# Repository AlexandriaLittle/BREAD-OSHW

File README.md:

# BREAD - Broadly Reconfigurable and Expandable Automation Device

## How to use
**Please check the Documentation folder for the original research paper and how-to guides!**

## Original Authors
The original project documentation is published in the open-access journal Hardware X 15 and is authored by Shane Oberloier, Nicholas G. Whisman, Finn Hafting, and Joshua M. Pearce. Other contributors have added to the body of work since. Please refer to the original sources (below) for important details about licensing, contributors, and any updates.

## About this repository
This is not an 'official' or even necessarily a current collection of all of these collected projects. Please see the links below to download from their original sources. The projects are collected here mostly for convenient access and learning.

## License
As the original project is licensed CC-BY-SA-4.0, this project is released under the same license. Social share image source https://www.appropedia.org/w/index.php?curid=122111.

## BREAD Links
- [Finn Hafting: Modularize your electronics with BREAD - YouTube](https://www.youtube.com/watch?v=OMPlVbqSqJ4)
- [Open Source Framework: Expandable Reconfigurable Data Acquisition Device (BREAD)](https://www.appropedia.org/Open_Source_Framework_for_a_Broadly_Expandable_and_Reconfigurable_Data_Acquisition_and_Automation_Device_(BREAD))
- [OSHE Bread Applications - Appropedia, the sustainability wiki](https://www.appropedia.org/OSHE_Bread_Applications)
- [GitHub - FHafting/BREAD](https://github.com/FHafting/BREAD)
- [OSF | BREAD](https://osf.io/u2h4g/overview)
- [OSF | LOAF_x04 Backplane](https://osf.io/7mk4w/overview)
- [OSF | BREAD LOAF_x08](https://osf.io/x4yqj/overview)
- [OSF | BREAD Slice - +/- 10A Current Sensor (SLC_CR10)](https://osf.io/ajmbe/overview)
- [OSF | BREAD Slice - +/- 20A Current Sensor (SLC_CR20)](https://osf.io/xe6cz/overview)
- [OSF | BREAD Slice - +/- 40A Current Sensor (SLC_CR40)](https://osf.io/xpgf8/overview)
- [OSF | BREAD Slice - 4 Channel Relay (SLC_RLAY)](https://osf.io/5vxws/overview)
- [OSF | BREAD Slice - Audio Analysis (SLC_AAFT)](https://osf.io/a8nk5/overview)
- [OSF | BREAD Slice - Bioreactor (SPECIALIZED) (SLC_PHDO)](https://osf.io/zbg98/overview)
- [OSF | BREAD Slice - BLDC Motor Controller](https://osf.io/w9rka/overview)
- [OSF | BREAD Slice - DC Motor Controller (SLC_DCMT)](https://osf.io/6aw9m/overview)
- [OSF | BREAD Slice - Field Solar Power (SLC_SOLR)](https://osf.io/9gm5h/overview)
- [OSF | BREAD Slice - MOLD(Mass Output and Logging Device)](https://osf.io/nm7je/overview)
- [OSF | BREAD Slice - Pressure Sensor](https://osf.io/86dz7/overview)
- [OSF | BREAD Slice - Pump Control Board (Specialized) (SLC_PUMP)](https://osf.io/4mzs8/overview)
- [OSF | BREAD Slice - Relay Heating Element Controller (SLC_RLHT)](https://osf.io/pf6gy/overview)
- [OSF | BREAD Slice - Servo Motor Controller (SLC_SERV)](https://osf.io/d7vks/overview)
- [OSF | BREAD Slice - Stepper Motor Controller (SLC_STEP)](https://osf.io/q8nkc/overview)
- [OSF | BREAD Slice - Template (SLC_TEMP)](https://osf.io/v5327/overview)
- [OSF | BREAD Slice - Text-to-Speech](https://osf.io/erbp6/overview)
- [OSF | BREAD Slice - Thermocouple Reader (SLC_THRM)](https://osf.io/sfehu/overview)
- [OSF | BREAD Slice - USB Port (SLC_USBP)](https://osf.io/j9rh5/overview)
- [OSF | BREAD Slice -- Analog Reader / FFT (SLC_LVAI)](https://osf.io/742ez/overview)
- [OSF | BREAD Slice -- Battery Management (SLC_BMS)](https://osf.io/yrmqu/overview)
- [OSF | BREAD Slice -- Buck Converter / Analog Signal Generator (SLC_BUCK)](https://osf.io/2xpnu/overview)
- [OSF | BREAD Slice-- Heating Element Controller (SLC_HEAT)](https://osf.io/m53fu/overview)
- [OSF | BREAD BUNS](https://osf.io/hbz92/overview)
- [OSF | BREAD CAN update](https://osf.io/3rnj4/overview)
- [OSF | BREAD DAQ](https://osf.io/wxt3s/overview)
- [OSF | BREAD Vision](https://osf.io/2htbm/overview)
- [OSF | Off-Grid BREAD](https://osf.io/98m6k/overview)
- [OSF | Integrated Open Source Pyrolysis Board based on BREAD](https://osf.io/3ugbn/overview)
- [Shane Oberloier | BREAD Contributor](https://osf.io/user/fntgd)
- [Nicholas Whisman | BREAD Contributor](https://osf.io/user/zs4mx?tab=2)
- [Finn Hafting | BREAD Contributor](https://osf.io/user/78mv4?tab=2)
- [BREAD References and Citations](https://ouci.dntb.gov.ua/en/works/lxXvAPQl/)
- [Open Source Hardware Enterprise](https://oshe.io/)
- [Original Project Logo](https://www.appropedia.org/w/index.php?curid=122111)

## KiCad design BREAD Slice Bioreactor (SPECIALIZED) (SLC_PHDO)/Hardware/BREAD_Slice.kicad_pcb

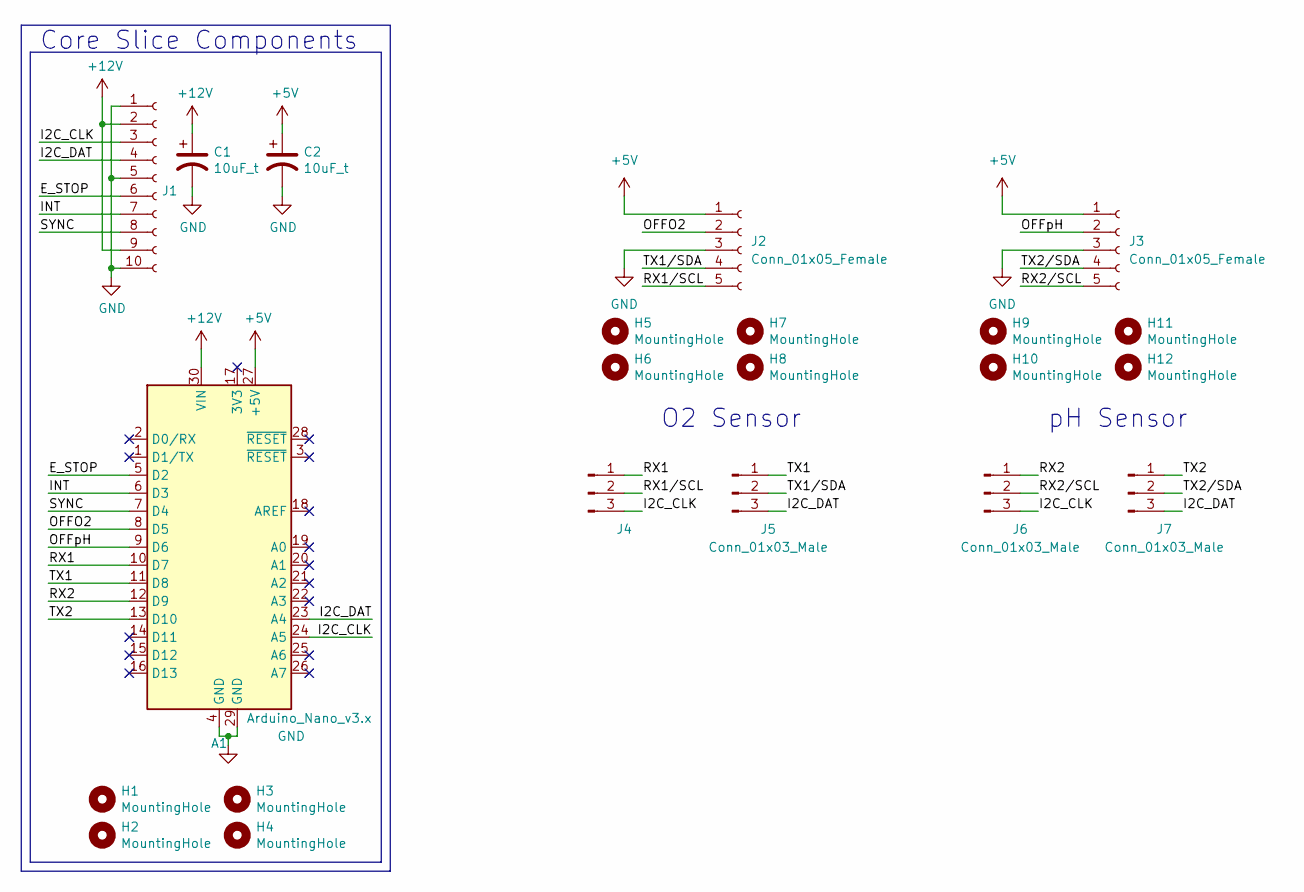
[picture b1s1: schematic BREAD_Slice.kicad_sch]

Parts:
A1: Arduino_Nano_v3.x; Arduino_Nano
C1, C2: 10uF_t; C_1206_3216Metric_Pad1.33x1.80mm_HandSolder; Part # T491C106K025AT
H1, H2, H3, H4, H5, H6, H7, H8, H9, H10, H11, H12: MountingHole; MountingHole_3.2mm_M3_DIN965_Pad
J1: Conn_01x10_Female; PinSocket_1x10_P2.54mm_Horizontal
J2, J3: Conn_01x05_Female; PinSocket_1x05_P2.54mm_Vertical
J4: (no value)
J5: Conn_01x03_Male
J6, J7: Conn_01x03_Male; PinSocket_1x03_P2.54mm_Vertical

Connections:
+5V: A1.27 (+5V), C2.1, J2.1, J3.1
+12V: A1.30 (VIN), C1.1, J1.2, J1.9
/E_STOP: A1.5 (D2), J1.6
/I2C_CLK: A1.24 (A5), J1.3, J4.3, J6.3
/I2C_DAT: A1.23 (A4), J1.4, J5.3, J7.3
/INT: A1.6 (D3), J1.7
/OFFO2: A1.8 (D5), J2.2
/OFFpH: A1.9 (D6), J3.2
/RX1: A1.10 (D7), J4.1
/RX1/SCL: J2.5, J4.2
/RX2: A1.12 (D9), J6.1
/RX2/SCL: J3.5, J6.2
/SYNC: A1.7 (D4), J1.8
/TX1: A1.11 (D8), J5.1
/TX1/SDA: J2.4, J5.2
/TX2: A1.13 (D10), J7.1
/TX2/SDA: J3.4, J7.2
GND: A1.4 (GND), A1.29 (GND), C1.2, C2.2, J1.1, J1.5, J1.10, J2.3, J3.3

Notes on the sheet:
O2 Sensor
pH Sensor
Core Slice Components

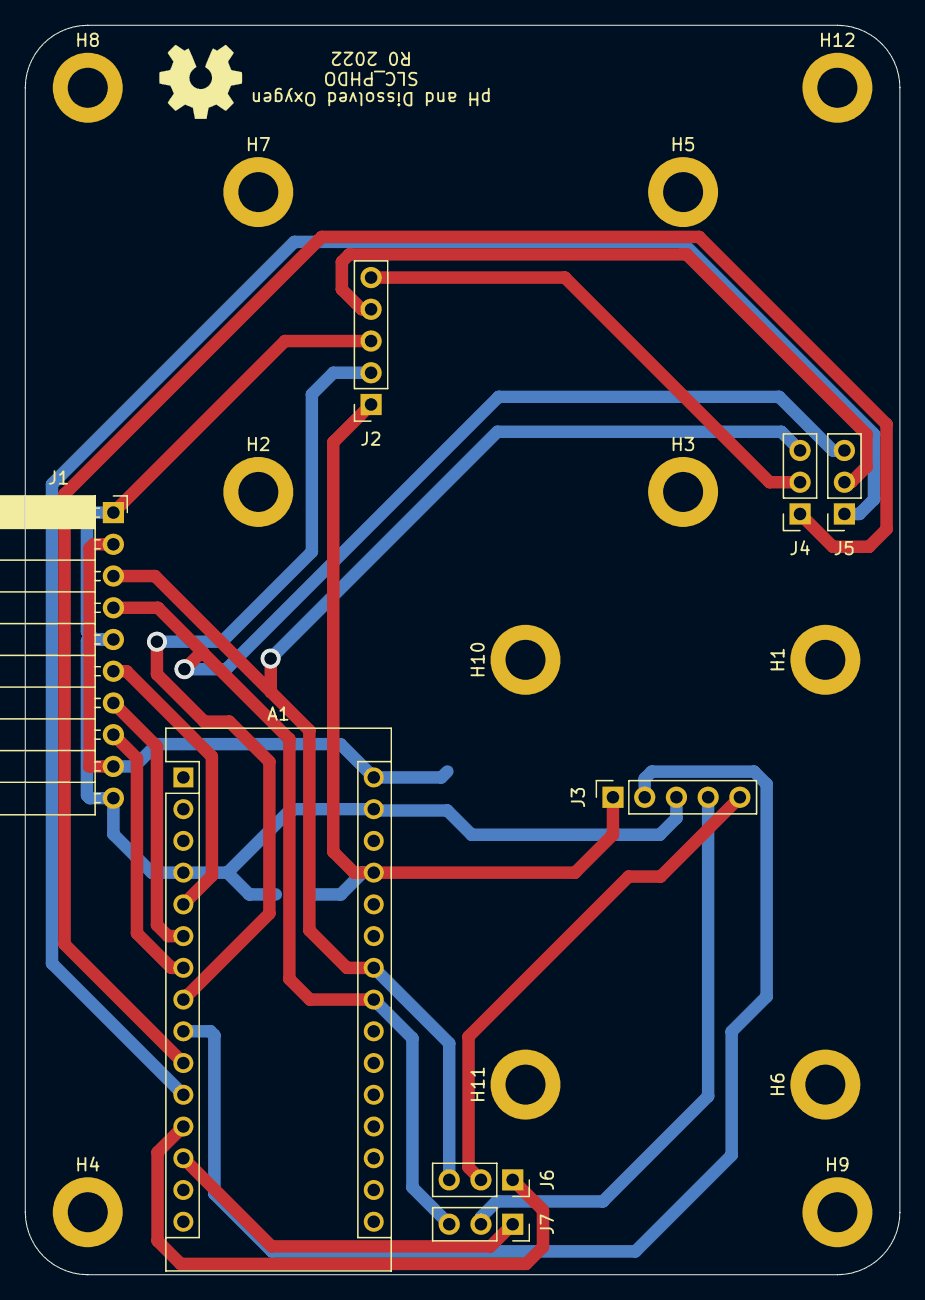
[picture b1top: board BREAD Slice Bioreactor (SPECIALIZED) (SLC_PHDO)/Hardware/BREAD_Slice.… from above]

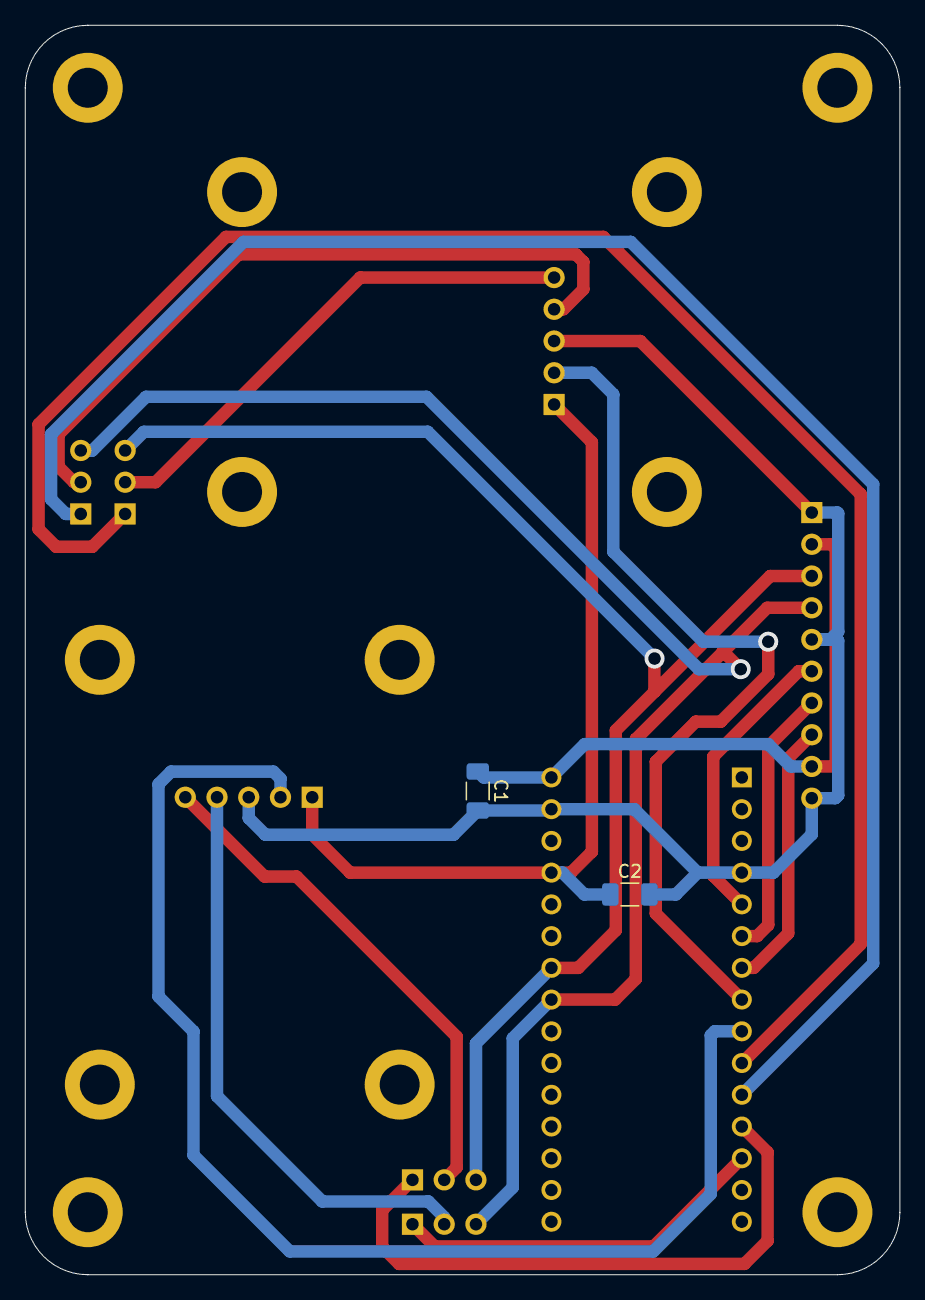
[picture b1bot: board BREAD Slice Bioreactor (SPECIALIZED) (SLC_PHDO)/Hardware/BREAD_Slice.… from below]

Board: 2 copper layers, 70.0 x 100.0 mm, 23 parts (2 on the bottom side), 18 nets.

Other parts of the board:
Logo1: Logo_Open_Hardware_Small; OSHW-Symbol_6.7x6mm_SilkScreen

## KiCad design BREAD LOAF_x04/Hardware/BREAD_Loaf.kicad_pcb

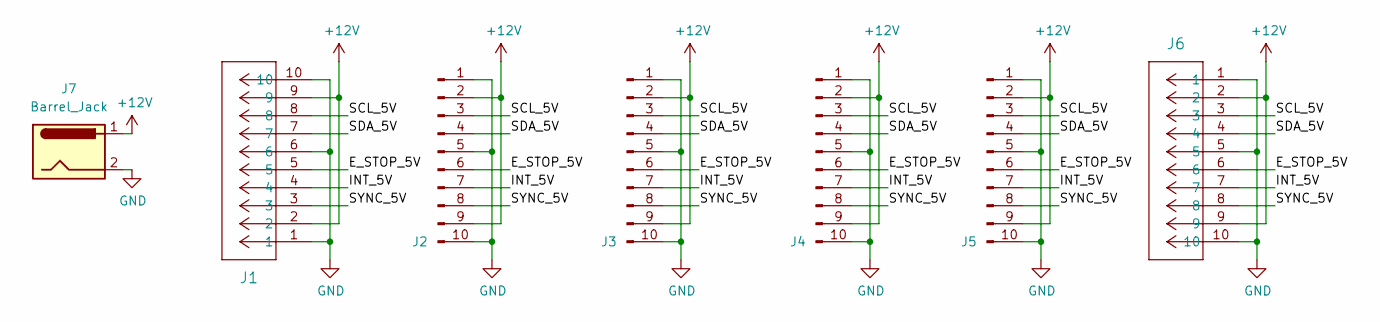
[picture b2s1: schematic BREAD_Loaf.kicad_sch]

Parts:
J1: PPPC101LGBN-RC; 1x10 RA Male Header 2.54mm Pitch
J2, J3, J4, J5: Conn_01x10_Male; BREAD 10-Pin Connector
J6: PPPC101LGBN-RC; PinSocket_1x10_P2.54mm_Horizontal
J7: Barrel_Jack; BarrelJack_CUI_PJ-063AH_Horizontal

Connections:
+12V: J1.2, J1.9, J2.2, J2.9, J3.2, J3.9, J4.2, J4.9, J5.2, J5.9, J6.2, J6.9, J7.1
/E_STOP_5V: J1.5, J2.6, J3.6, J4.6, J5.6, J6.6
/INT_5V: J1.4, J2.7, J3.7, J4.7, J5.7, J6.7
/SCL_5V: J1.8, J2.3, J3.3, J4.3, J5.3, J6.3
/SDA_5V: J1.7, J2.4, J3.4, J4.4, J5.4, J6.4
/SYNC_5V: J1.3, J2.8, J3.8, J4.8, J5.8, J6.8
GND: J1.1, J1.6, J1.10, J2.1, J2.5, J2.10, J3.1, J3.5, J3.10, J4.1, J4.5, J4.10, J5.1, J5.5, J5.10, J6.1, J6.5, J6.10, J7.2

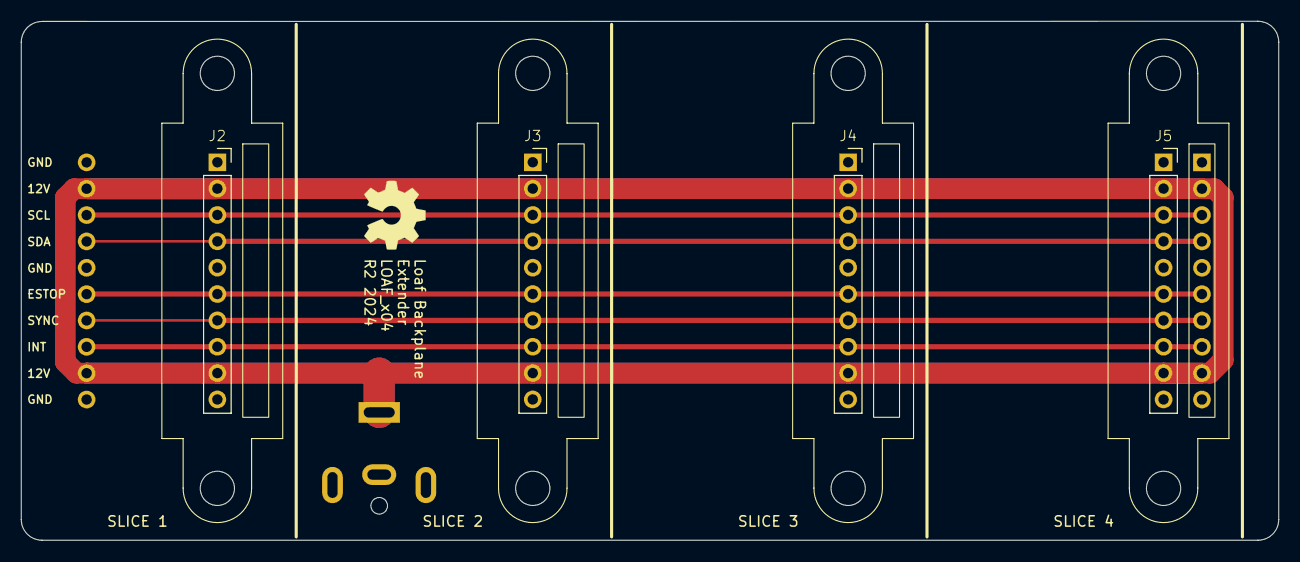
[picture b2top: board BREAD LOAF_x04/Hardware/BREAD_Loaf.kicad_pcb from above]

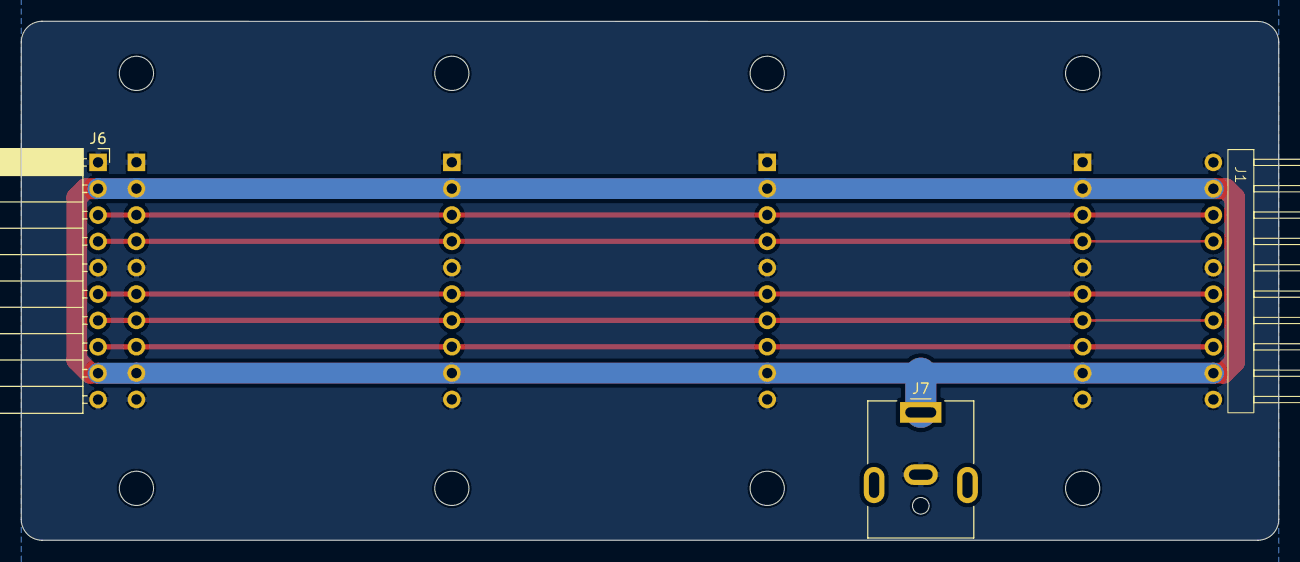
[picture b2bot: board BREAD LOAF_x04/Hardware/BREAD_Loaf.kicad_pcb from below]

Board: 2 copper layers, 121.2 x 50.0 mm, 8 parts (3 on the bottom side), 7 nets.

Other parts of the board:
Logo1: Logo_Open_Hardware_Small; OSHW-Symbol_6.7x6mm_SilkScreen

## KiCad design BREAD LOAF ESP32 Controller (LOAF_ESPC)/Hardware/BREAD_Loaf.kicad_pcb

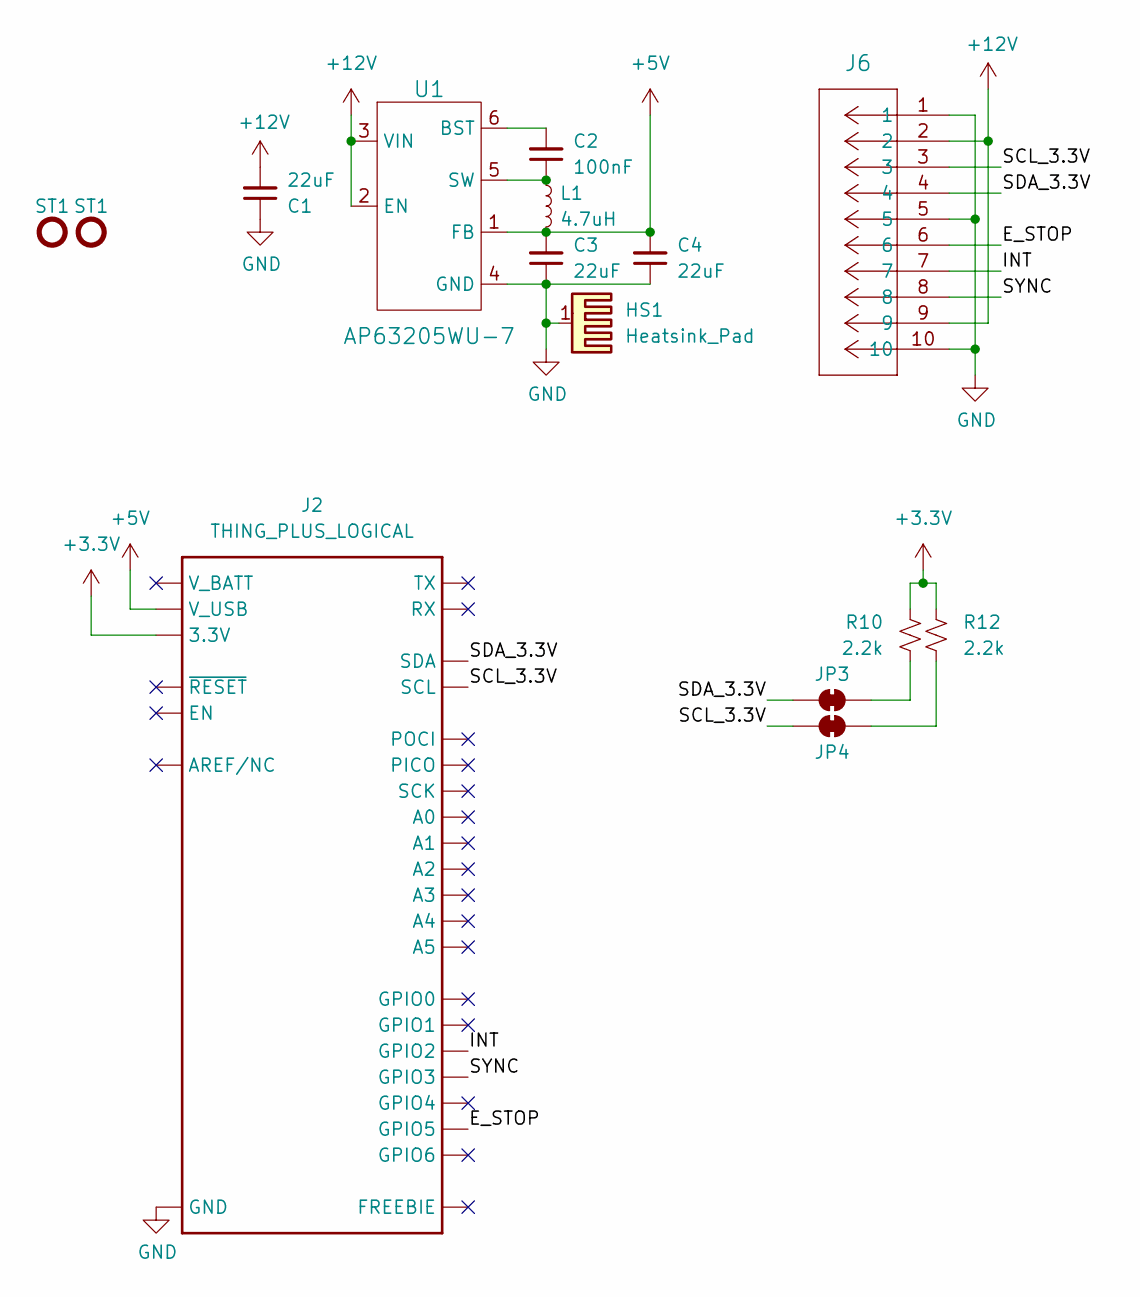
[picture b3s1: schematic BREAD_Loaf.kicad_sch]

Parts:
C1, C3, C4: 22uF; C_1206_3216Metric
C2: 100nF; C_1206_3216Metric
HS1: Heatsink_Pad; Thermal Pad
J2: THING_PLUS_LOGICAL; ESP_THING_PLUS
J6: PPPC101LGBN-RC; PinSocket_1x10_P2.54mm_Horizontal
JP3, JP4: SMT-JUMPER_2_NC_TRACE_SILK
L1: 4.7uH; L_1210_3225Metric
R10, R12: 2.2k; R_0603_1608Metric
ST1: Stand_off; STAND-OFF
U1: AP63205WU-7; TSOT-23-6

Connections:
+3.3V: J2.27 (3.3V), R10.1, R12.1
+5V: C3.2, C4.2, J2.10 (V_USB), L1.2; also elsewhere on the board
+12V: C1.2, J6.2, J6.9; also elsewhere on the board
/E_STOP: J2.4 (GPIO5), J6.6
/INT: J2.7 (GPIO2), J6.7
/SCL_3.3V: J2.2 (SCL), J6.3, JP4.2 (B)
/SDA_3.3V: J2.1 (SDA), J6.4, JP3.2 (B)
/SYNC: J2.6 (GPIO3), J6.8
GND: C1.1, C3.1, C4.1, HS1.1, J2.25 (GND), J6.1, J6.5, J6.10; also elsewhere on the board
unnamed: JP3.1 (A), R10.2
unnamed: JP4.1 (A), R12.2
unnamed 11: C2.2; also elsewhere on the board
unnamed 12: C2.1, L1.1; also elsewhere on the board

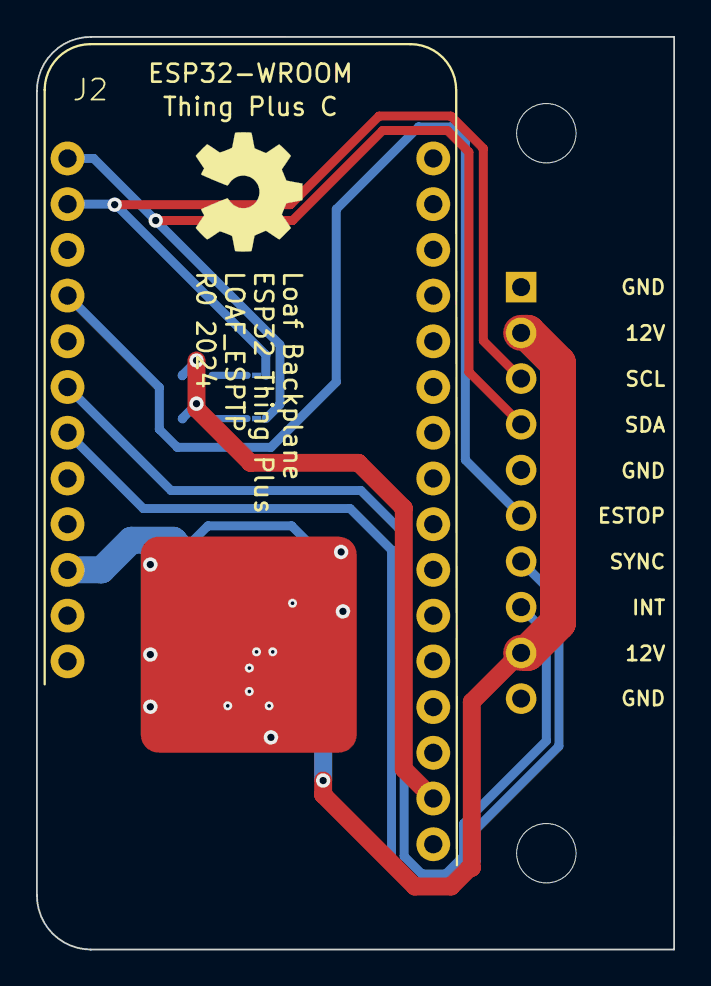
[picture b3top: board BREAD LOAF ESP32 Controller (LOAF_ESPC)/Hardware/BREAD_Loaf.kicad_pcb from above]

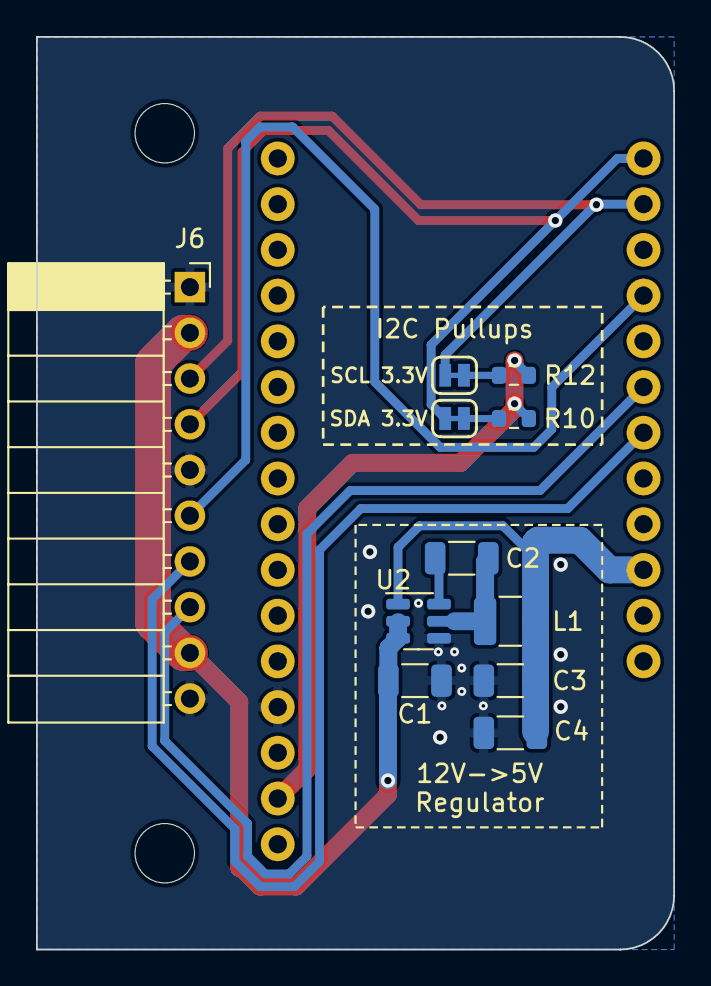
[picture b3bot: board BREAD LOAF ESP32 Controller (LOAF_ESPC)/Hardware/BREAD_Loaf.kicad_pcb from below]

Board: 2 copper layers, 35.4 x 50.7 mm, 16 parts (11 on the bottom side), 13 nets.

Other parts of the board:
Logo1: Logo_Open_Hardware_Small; OSHW-Symbol_6.7x6mm_SilkScreen
ST2: Stand_off; STAND-OFF
U2: AP63205WU-7; TSOT-23-6

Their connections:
+5V: U2.1 (FB); also elsewhere on the board
+12V: U2.2 (EN), U2.3 (VIN); also elsewhere on the board
GND: U2.4 (GND); also elsewhere on the board
unnamed 11: U2.6 (BST); also elsewhere on the board
unnamed 12: U2.5 (SW); also elsewhere on the board

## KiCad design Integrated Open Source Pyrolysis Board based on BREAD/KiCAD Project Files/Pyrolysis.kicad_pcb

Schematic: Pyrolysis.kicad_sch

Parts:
A1, A2, A3, A4, A5: Arduino_Nano_v3.x; Arduino_Nano
C1, C2, C3, C4, C8, C9, C12, C13, C14, C15, C16: 0.01 uF; C_1206_3216Metric_Pad1.33x1.80mm_HandSolder
C5, C10, C11: 10uF; C_1206_3216Metric_Pad1.33x1.80mm_HandSolder
C6, C7, C17: 10 nF; C_1206_3216Metric_Pad1.33x1.80mm_HandSolder
D1, D2, D3, D4, D5, D6, D7, D8, D9, D10: General_Purpose_Diode; D_DO-35_SOD27_P7.62mm_Horizontal; Part # 1N914BWS
F1, F2, F3, F4, F5, F6, F7, F8, F9, F10: 10A; Fuse_Holder; Part # 3522-2
FB1, FB2, FB3, FB4, FB5, FB6, FB7, FB8, FB9, FB10, FB11, FB12, FB13, FB14, FB15, FB16, FB17, FB18, FB19, FB20, FB21, FB22: Ferrite_Bead_Small; R_1206_3216Metric_Pad1.30x1.75mm_HandSolder
H1, H2, H3, H4: MountingHole; MountingHole_3.2mm_M3_DIN965_Pad
J1, J2, J3, J4, J5, J6, J7, J9, J11, J12, J15, J16, J17, J21, J22, J23, J27, J28, J29, J30, J32, J33, J34, J36, J37, J39, J40, J41, J43, J44, J45, J47, J48: Term_2; TerminalBlock_Phoenix_MKDS-1,5-2_1x02_P5.00mm_Horizontal; Part # 1935161
J8: Conn_01x03_Male; PinSocket_1x03_P2.54mm_Vertical
J10: Screw_Terminal_01x04; TerminalBlock_TE_282834-4_1x04_P2.54mm_Horizontal
J13: Conn_01x03_Male; PinHeader_1x03_P2.54mm_Vertical
J26: Barrel_Jack; BarrelJack_CUI_PJ-102AH_Horizontal
K1, K2, K3, K4, K5, K6, K7, K8, K9, K10: G5Q-1; Relay_SPDT_Omron-G5Q-1
R1: 2.2 k; R_1206_3216Metric_Pad1.30x1.75mm_HandSolder
U1, U4, U5, U8, U11, U14, U16, U18, U20, U22: TCMT1100; SOP-4_4.4x2.6mm_P1.27mm
U2, U3, U6, U7, U10, U13, U15, U17, U19, U21, U23: MAX6675ISA+; SO08-MAX6675
U12: AP1117-50; SOT-223-3_TabPin2
U24: LMD18200; TO-220-11_P3.4x5.08mm_StaggerOdd_Lead4.85mm_Vertical

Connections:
+5V: A1.27 (+5V), A2.27 (+5V), A3.27 (+5V), A4.27 (+5V), A5.27 (+5V), C11.1, J10.3, U2.4 (VCC), U3.4 (VCC), U6.4 (VCC), U7.4 (VCC), U10.4 (VCC), U12.2 (VO), U13.4 (VCC), U15.4 (VCC), U17.4 (VCC), U19.4 (VCC), U21.4 (VCC), U23.4 (VCC)
+12V: C10.1, F1.2, F2.2, F3.2, F4.2, F5.2, F6.2, F7.2, F8.2, F9.2, F10.2, J8.2, J26.1, U12.3 (VI)
/3V3: A3.17 (3V3)
/A1: A3.19 (A0), J10.1
/B1: A3.20 (A1), J10.2
/BR1: A3.9 (D6), U24.4 (BRAKE)
/CLK1: A2.16 (D13), U3.5 (SCK), U7.5 (SCK), U10.5 (SCK)
/CLK2: A4.16 (D13), U13.5 (SCK), U15.5 (SCK), U17.5 (SCK)
/CLK3: A5.16 (D13), U19.5 (SCK), U21.5 (SCK), U23.5 (SCK)
/CLK4: A1.16 (D13), U2.5 (SCK), U6.5 (SCK)
/CSEN1: A3.25 (A6), C17.1, R1.1, U24.8 (CURRENT_SENSE_OUTPUT)
/CUST1: J8.1, J11.1
/DATA1: A2.15 (D12), U3.7 (SO), U7.7 (SO), U10.7 (SO)
/DATA2: A4.15 (D12), U13.7 (SO), U15.7 (SO), U17.7 (SO)
/DATA3: A5.15 (D12), U19.7 (SO), U21.7 (SO), U23.7 (SO)
/DATA4: A1.15 (D12), U2.7 (SO), U6.7 (SO)
/DIR1: A3.10 (D7), U24.3 (DIRECTION)
/I2C_CLK: A1.24 (A5), A2.24 (A5), A3.24 (A5), A4.24 (A5), A5.24 (A5), J13.2
/I2C_DAT: A1.23 (A4), A2.23 (A4), A3.23 (A4), A4.23 (A4), A5.23 (A4), J13.1
/MC1: A3.12 (D9), U24.5 (PWM)
/PWM1: A2.8 (D5), U1.1
/PWM2: A2.9 (D6), U5.1
/PWM3: A2.10 (D7), U8.1
/PWM4: A4.8 (D5), U11.1
/PWM5: A4.9 (D6), U14.1
/PWM6: A4.10 (D7), U16.1
/PWM7: A5.8 (D5), U18.1
/PWM8: A5.9 (D6), U20.1
/PWM9: A5.10 (D7), U22.1
/PWM10: A1.10 (D7), U4.1
/SS1: A2.12 (D9), U3.6 (~CS)
/SS2: A2.13 (D10), U7.6 (~CS)
/SS3: A2.14 (D11), U10.6 (~CS)
/SS4: A4.12 (D9), U13.6 (~CS)
/SS5: A4.13 (D10), U15.6 (~CS)
/SS6: A4.14 (D11), U17.6 (~CS)
/SS7: A5.12 (D9), U19.6 (~CS)
/SS8: A5.13 (D10), U21.6 (~CS)
/SS9: A5.14 (D11), U23.6 (~CS)
/SS10: A1.13 (D10), U2.6 (~CS)
/SS11: A1.14 (D11), U6.6 (~CS)
/T+1: C1.1, FB1.1, U3.3 (T+)
/T+2: C4.1, FB5.1, U7.3 (T+)
/T+3: C8.1, FB7.1, U10.3 (T+)
/T+4: C9.1, FB9.1, U13.3 (T+)
/T+5: C12.1, FB11.1, U15.3 (T+)
/T+6: C13.1, FB13.1, U17.3 (T+)
/T+7: C14.1, FB15.1, U19.3 (T+)
/T+8: C15.1, FB17.1, U21.3 (T+)
/T+9: C16.1, FB19.1, U23.3 (T+)
/T+10: C2.1, FB3.1, U2.3 (T+)
/T+11: C3.1, FB21.1, U6.3 (T+)
/THRM1: A3.8 (D5), U24.9 (~THERMAL_FLAG_OUTPUT)
GND: A1.4 (GND), A1.29 (GND), A2.4 (GND), A2.29 (GND), A3.4 (GND), A3.29 (GND), A4.4 (GND), A4.29 (GND), A5.4 (GND), A5.29 (GND), C1.2, C2.2, C3.2, C4.2, C5.2, C8.2, C9.2, C10.2, C11.2, C12.2, C13.2, C14.2, C15.2, C16.2, C17.2, FB2.1, FB4.1, FB6.1, FB8.1, FB10.1, FB12.1, FB14.1, FB16.1, FB18.1, FB20.1, FB22.1, J6.2, J7.2, J10.4, J11.2, J13.3, J16.2, J22.2, J26.2, J28.2, J33.2, J37.2, J40.2, J44.2, J48.2, R1.2, U1.2, U1.3, U2.1 (GND), U2.2 (T-), U3.1 (GND), U3.2 (T-), U4.2, U4.3, U5.2, U5.3, U6.1 (GND), U6.2 (T-), U7.1 (GND), U7.2 (T-), U8.2, U8.3, U10.1 (GND), U10.2 (T-), U11.2, U11.3, U12.1 (GND), U13.1 (GND), U13.2 (T-), U14.2, U14.3, U15.1 (GND), U15.2 (T-), U16.2, U16.3, U17.1 (GND), U17.2 (T-), U18.2, U18.3, U19.1 (GND), U19.2 (T-), U20.2, U20.3, U21.1 (GND), U21.2 (T-), U22.2, U22.3, U23.1 (GND), U23.2 (T-), U24.7 (GND)
unnamed: C5.1, J8.3, U24.6 (VS)
unnamed: C6.1, J12.1, U24.2 (OUTPUT1)
unnamed: C6.2, U24.1 (BOOTSTRAP1)
unnamed: C7.1, U24.11 (BOOTSTRAP2)
unnamed: C7.2, J12.2, U24.10 (OUTPUT2)
unnamed: D1.1 (K), F1.1, K1.5
unnamed: D1.2 (A), K1.1, U1.4
unnamed: D2.1 (K), F2.1, K2.5
unnamed: D2.2 (A), K2.1, U4.4
unnamed: D3.1 (K), F3.1, K3.5
unnamed: D3.2 (A), K3.1, U5.4
unnamed: D4.1 (K), F4.1, K4.5
unnamed: D4.2 (A), K4.1, U8.4
unnamed: D5.1 (K), F5.1, K5.5
unnamed: D5.2 (A), K5.1, U11.4
unnamed: D6.1 (K), F6.1, K6.5
unnamed: D6.2 (A), K6.1, U14.4
unnamed: D7.1 (K), F7.1, K7.5
unnamed: D7.2 (A), K7.1, U16.4
unnamed: D8.1 (K), F8.1, K8.5
unnamed: D8.2 (A), K8.1, U18.4
unnamed: D9.1 (K), F9.1, K9.5
unnamed: D9.2 (A), K9.1, U20.4
unnamed: D10.1 (K), F10.1, K10.5
unnamed: D10.2 (A), K10.1, U22.4
unnamed: FB1.2, J1.2
unnamed: FB2.2, J1.1
unnamed: FB3.2, J2.2
unnamed: FB4.2, J2.1
unnamed: FB5.2, J9.2
unnamed: FB6.2, J9.1
unnamed: FB7.2, J17.2
unnamed: FB8.2, J17.1
unnamed: FB9.2, J23.2
unnamed: FB10.2, J23.1
unnamed: FB11.2, J30.2
unnamed: FB12.2, J30.1
unnamed: FB13.2, J34.2
unnamed: FB14.2, J34.1
unnamed: FB15.2, J29.2
unnamed: FB16.2, J29.1
unnamed: FB17.2, J41.2
unnamed: FB18.2, J41.1
unnamed: FB19.2, J45.2
unnamed: FB20.2, J45.1
unnamed: FB21.2, J3.2
unnamed: FB22.2, J3.1
unnamed: J4.1, K2.4
unnamed: J4.2, K2.3
unnamed: J5.1, K1.4
unnamed: J5.2, K1.3
unnamed: J6.1, K1.2
unnamed: J7.1, K2.2
unnamed: J15.1, K3.4
unnamed: J15.2, K3.3
unnamed: J16.1, K3.2
unnamed: J21.1, K4.4
unnamed: J21.2, K4.3
unnamed: J22.1, K4.2
unnamed: J27.1, K5.4
unnamed: J27.2, K5.3
unnamed: J28.1, K5.2
unnamed: J32.1, K6.4
unnamed: J32.2, K6.3
unnamed: J33.1, K6.2
unnamed: J36.1, K7.4
unnamed: J36.2, K7.3
unnamed: J37.1, K7.2
unnamed: J39.1, K8.4
unnamed: J39.2, K8.3
unnamed: J40.1, K8.2
unnamed: J43.1, K9.4
unnamed: J43.2, K9.3
unnamed: J44.1, K9.2
unnamed: J47.1, K10.4
unnamed: J47.2, K10.3
unnamed: J48.1, K10.2

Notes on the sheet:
Control Arduino 1
Thermocouples
Motor
Control Arduino 5
Control Arduino 2
Heater
Control Arduino 4
Heaters
Control Arduino 3
Core Components

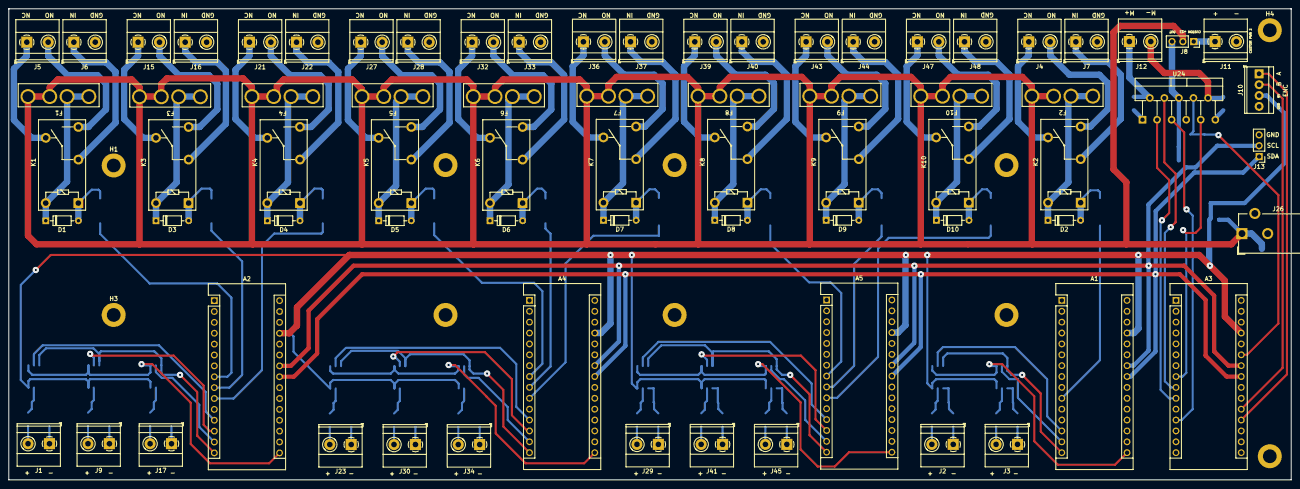
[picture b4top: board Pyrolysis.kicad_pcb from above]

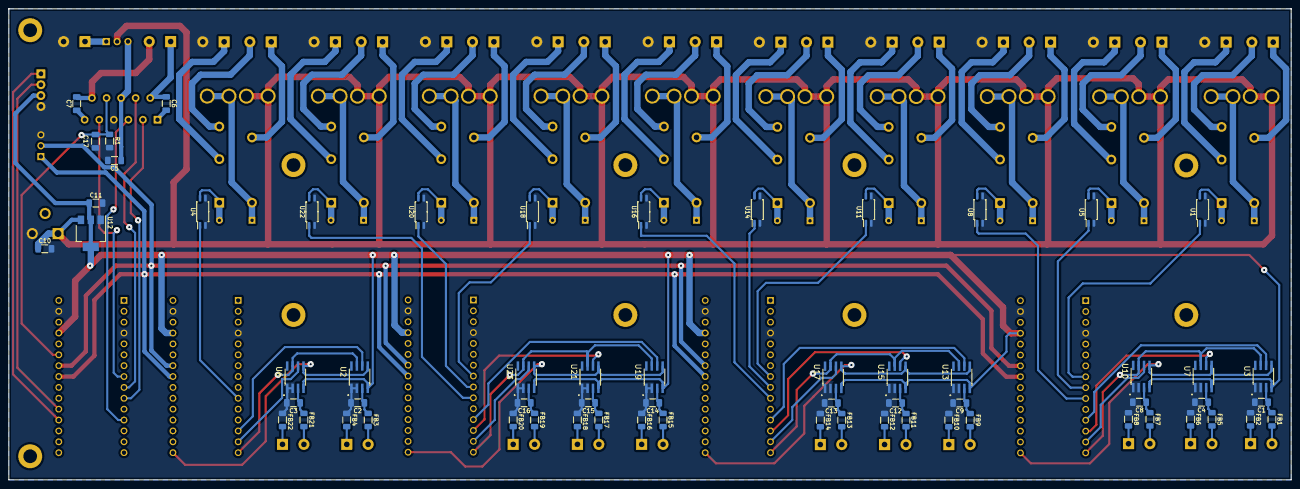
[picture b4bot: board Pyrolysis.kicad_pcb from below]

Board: 2 copper layers, 299.5 x 110.0 mm, 138 parts (62 on the bottom side), 130 nets.

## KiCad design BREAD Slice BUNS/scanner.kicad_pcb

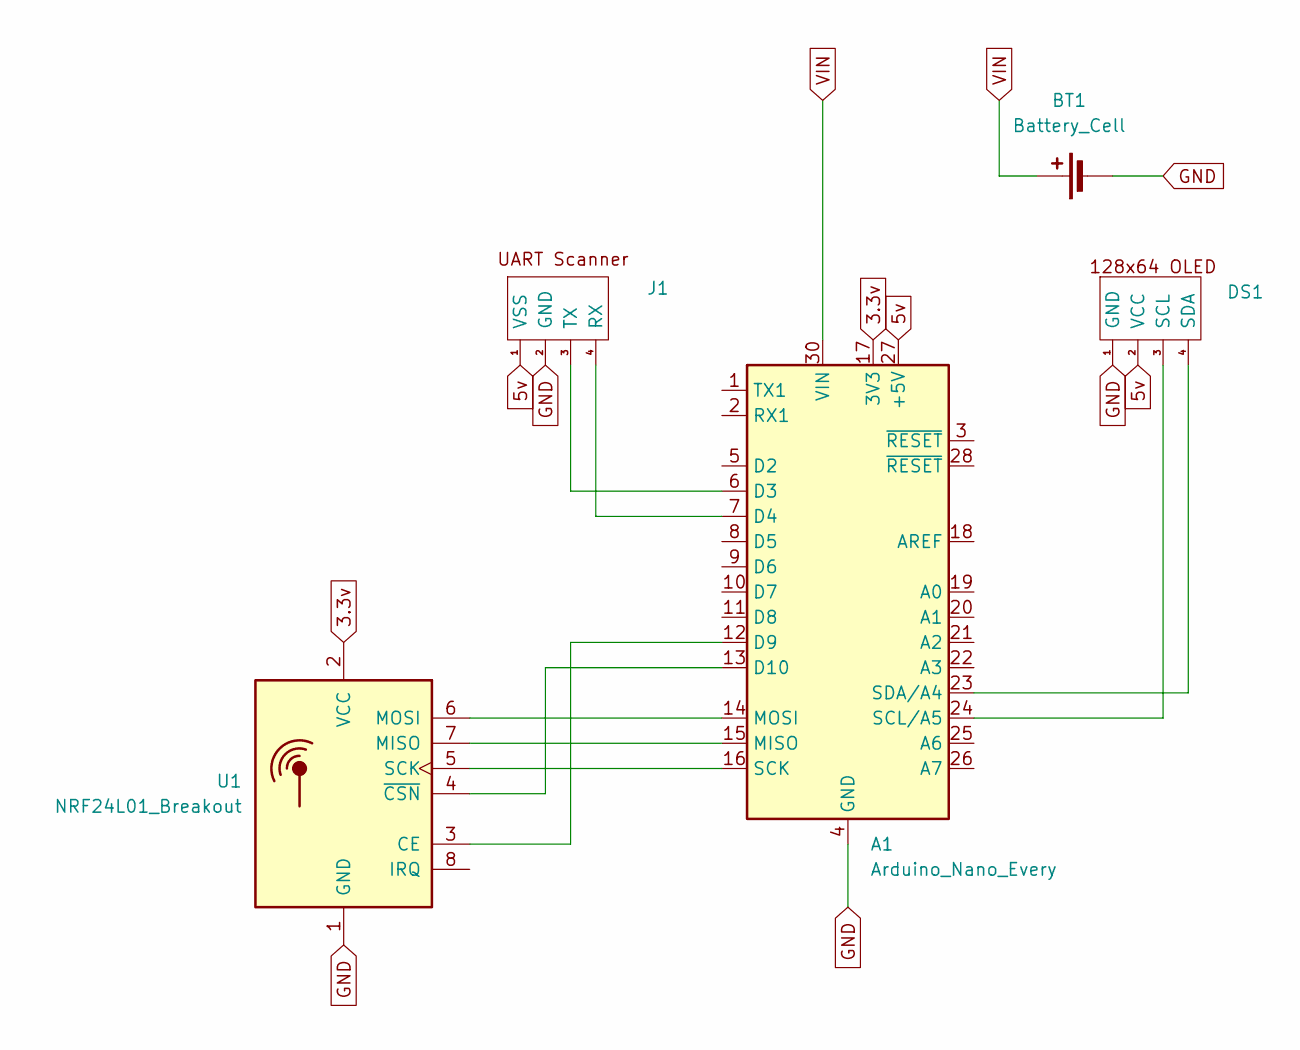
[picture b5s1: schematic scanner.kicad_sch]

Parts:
A1: Arduino_Nano_Every; Arduino_Nano
BT1: Battery_Cell; BatteryConnection
DS1: WireConnection
J1: WireConnection
U1: NRF24L01_Breakout; nRF24L01_Breakout

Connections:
3.3v: A1.17 (3V3), U1.2 (VCC)
5v: A1.27 (+5V), DS1.2 (VCC), J1.1 (VSS)
GND: A1.4 (GND), A1.29 (GND), BT1.2 (-), DS1.1 (GND), J1.2 (GND), U1.1 (GND)
unnamed: A1.6 (D3), J1.3 (TX)
unnamed: A1.7 (D4), J1.4 (RX)
unnamed: A1.12 (D9), U1.3 (CE)
unnamed: A1.13 (D10), U1.4 (~CSN)
unnamed: A1.15 (MISO), U1.7 (MISO)
unnamed: A1.14 (MOSI), U1.6 (MOSI)
unnamed: A1.16 (SCK), U1.5 (SCK)
unnamed: A1.24 (SCL/A5), DS1.3 (SCL)
unnamed: A1.23 (SDA/A4), DS1.4 (SDA)
VIN: A1.30 (VIN), BT1.1 (+)

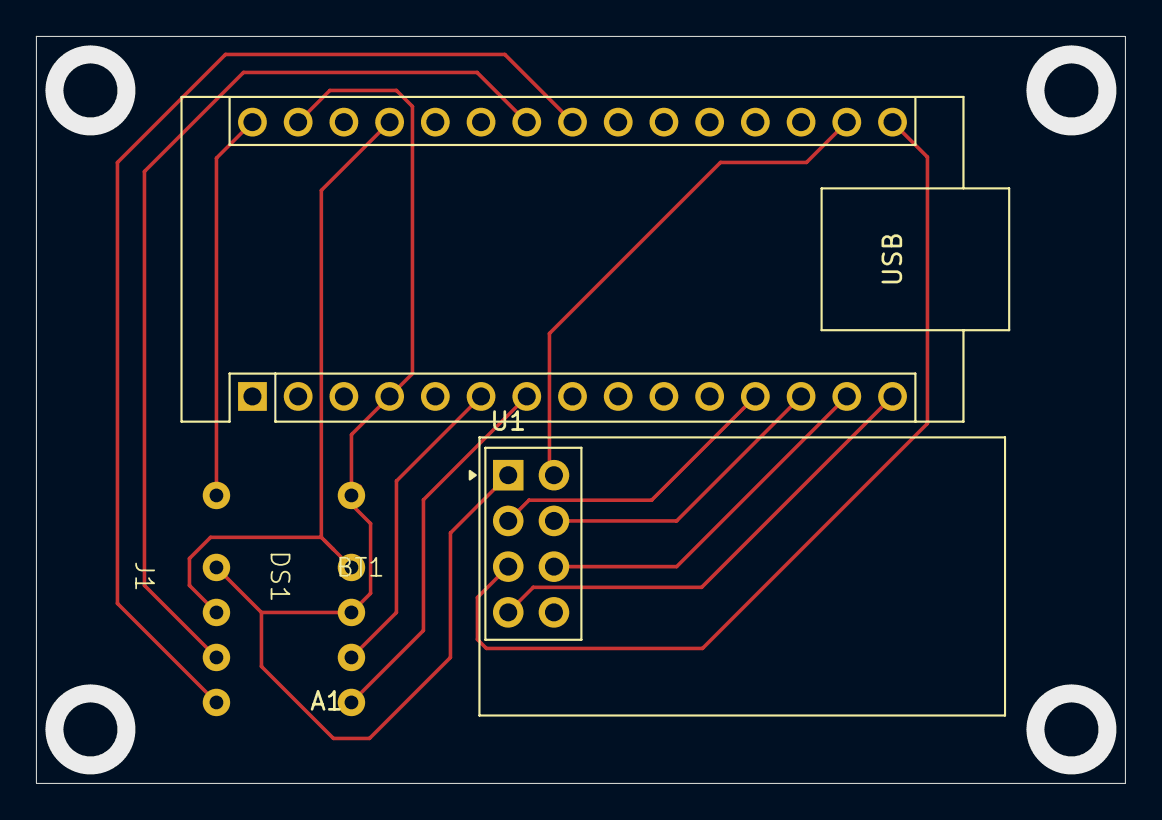
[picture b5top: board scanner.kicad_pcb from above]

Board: 2 copper layers, 60.5 x 41.5 mm, 5 parts (0 on the bottom side), 13 nets.
